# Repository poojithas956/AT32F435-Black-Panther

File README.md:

# AT32F435 - Black Panther

<h4>This is my most favorate Microcontroller, hence I wanted to design & build a compact, cute, powerful packed Dev Board. 

It features crucial sensors like ICM-42688-P for 6 axis Gyroscope, BMP581 for Barometric Pressure.

Can be used in wide variety of projects, powerful enough.
From being a custom microcontroller turned into a Flight controller, Can be used for Telemetry, IoT devices, Automation, etc...</h4>

## Layout

6 Layer PCB 4 mil / 4mil 

Stack:
Signal
Ground
Power
Ground
Signal

Consists 79 nets with 263 Pads, 142 Vias, 544 Track Segments

## Gallery

## Bill of Materials

| # | Item / MPN | Type | Vendor | Package | Qty | Unit Price | Line Total | Funding |
|---:|---|---|---|---|---:|---:|---:|---|
| 1 | [FRC0603F3571TS](https://www.lcsc.com/product-detail/C2933206.html) — 3.57kΩ ±1% 100mW 0603 Thick Film Resistor | Part | FOJAN | 0603 | 100 | $0.0012 | $0.12 | Grant |
| 2 | [X32258MOB4SI](https://www.lcsc.com/product-detail/C2682775.html) — Crystal 8MHz ±10ppm 12pF 150Ω SMD3225-4P | Part | YXC Crystal Oscillators | SMD3225-4P | 5 | $0.1993 | $1.00 | Grant |
| 3 | [AT32F435RGT7](https://www.lcsc.com/product-detail/C3029577.html) — ARM Cortex-M4 32 Bit 288MHz LQFP-64(10x10) Microcontrollers | Part | ARTERY | LQFP-64(10x10) | 1 | $4.3654 | $4.37 | Already own |
| 4 | [BQ24072RGTR](https://www.lcsc.com/product-detail/C140288.html) — 4.35V~6.6V Lithium Battery 1 1.5A QFN-16-EP(3x3) Battery Chargers RoHS | Part | TI | QFN-16-EP(3x3) | 1 | $1.0593 | $1.06 | Grant |
| 5 | [DFE252012P-1R0M=P2](https://www.lcsc.com/product-detail/C882955.html) — 4.3A 1uH ±20% 42mΩ 4.3A 1008 Fixed Inductors RoHS | Part | muRata | 1008 | 5 | $0.1244 | $0.62 | Grant |
| 6 | [TPS631000DRLR](https://www.lcsc.com/product-detail/C5219190.html) — Buck-Boost Switching Regulator IC Adjustable 1.2V~5.3V 2A SOT-583 | Part | TI | SOT-583 | 1 | $0.4560 | $0.46 | Grant |
| 7 | [TPD2EUSB30DRTR](https://www.lcsc.com/product-detail/C5182099.html) — 18VC Clamp TVS DIODE SOT(9x3) | Part | TECH PUBLIC | SOT(9x3) | 5 | $0.1979 | $0.99 | Grant |
| 8 | [BMP581](https://www.lcsc.com/product-detail/C5362283.html) — 30Kpa~1.25bar LGA-10(2x2) Pressure Sensors, Transducers RoHS | Part | Bosch | LGA-10(2x2) | 1 | $2.3423 | $2.34 | Grant |
| 9 | [ICM-42688-P](https://www.lcsc.com/product-detail/C1850418.html) — LGA-14(2.5x3) IMUs (Inertial Measurement Units) RoHS | Part | TDK InvenSense | LGA-14(2.5x3) | 1 | $25.8192 | $25.82 | Grant |
| 10 | [HX 3x4x2-2P-1.6N-04](https://www.lcsc.com/product-detail/C55073343.html) — 4mm 1.6N 12V 3mm Round Button SPST 50mA SMD Tactile Switch | Part | hanxia | SMD,4x3mm | 20 | $0.0274 | $0.55 | Grant |
| 11 | [CR16330J](https://www.lcsc.com/product-detail/C5602400.html) — 33Ω 100mW Thick Film Resistor ±100ppm/℃ ±5% 0603 Chip Resistor | Part | Meritek | 0603 | 1 | $0.0036 | $0.01 | Grant |
| 12 | [FRC0603F9102TS](https://www.lcsc.com/product-detail/C2907077.html) — 91kΩ ±1% 100mW 0603 Thick Film Resistor | Part | FOJAN | 0603 | 100 | $0.0016 | $0.16 | Grant |
| 13 | [RT0603BRD07511KL](https://www.lcsc.com/product-detail/C861454.html) — 511kΩ 100mW 75V Thin Film Resistor ±25ppm/℃ ±0.1% 0603 Chip Resistor | Part | YAGEO | 0603 | 20 | $0.0396 | $0.79 | Grant |
| 14 | [RC0603FR-074K7L](https://www.lcsc.com/product-detail/C99782.html) — 100mW 4.7kΩ 75V Thick Film Resistor ±100ppm/℃ ±1% 0603 Chip Resistor | Part | YAGEO | 0603 | 100 | $0.0032 | $0.32 | Grant |
| 15 | [RC0603FR-07100KL](https://www.lcsc.com/product-detail/C14675.html) — 100mW 100kΩ 75V Thick Film Resistor ±100ppm/℃ ±1% 0603 Chip Resistor | Part | YAGEO | 0603 | 100 | $0.0021 | $0.21 | Grant |
| 16 | [RC0603FR-071KL](https://www.lcsc.com/product-detail/C22548.html) — 100mW 1kΩ 75V Thick Film Resistor ±100ppm/℃ ±1% 0603 Chip Resistor | Part | YAGEO | 0603 | 100 | $0.0036 | $0.36 | Grant |
| 17 | [CL10A475KP8NNNC](https://www.lcsc.com/product-detail/C1705.html) — 4.7uF ±10% 10V Ceramic Capacitor X5R 0603 | Part | Samsung Electro-Mechanics | 0603 | 50 | $0.0128 | $0.64 | Grant |
| 18 | [RC0603FR-072K2L](https://www.lcsc.com/product-detail/C114662.html) — 100mW 2.2kΩ 75V Thick Film Resistor ±100ppm/℃ ±1% 0603 Chip Resistor | Part | YAGEO | 0603 | 100 | $0.0019 | $0.19 | Grant |
| 19 | [RC0603FR-0710KL](https://www.lcsc.com/product-detail/C98220.html) — 100mW 10kΩ 75V Thick Film Resistor ±100ppm/℃ ±1% 0603 Chip Resistor | Part | YAGEO | 0603 | 100 | $0.0023 | $0.23 | Grant |
| 20 | [FRC0603F5602TS](https://www.lcsc.com/product-detail/C2907053.html) — 56kΩ ±1% 100mW 0603 Thick Film Resistor | Part | FOJAN | 0603 | 100 | $0.0018 | $0.18 | Grant |
| 21 | [XL-1005UBC](https://www.lcsc.com/product-detail/C22355736.html) — Blue 465nm LED Indication - Discrete 3.3V 0402 | Part | XINGLIGHT | 0402 | 50 | $0.0081 | $0.41 | Grant |
| 22 | [XL-1005UGC](https://www.lcsc.com/product-detail/C965793.html) — Emerald Green 531nm LED Indication - Discrete 3V 0402 | Part | XINGLIGHT | 0402 | 50 | $0.0090 | $0.45 | Grant |
| 23 | [SZYY0603Y](https://www.lcsc.com/product-detail/C434424.html) — Yellow 596nm LED Indication - Discrete 2.4V 0603 | Part | Yongyu Photoelectric | 0603 | 50 | $0.0150 | $0.75 | Grant |
| 24 | [BLM18PG121SN1D](https://www.lcsc.com/product-detail/C14709.html) — 120Ω@100MHz 1 Line Ferrite Bead 0603 2A 50mΩ | Part | muRata | 0603 | 50 | $0.0142 | $0.71 | Grant |
| 25 | [PZ254V-11-04P](https://www.lcsc.com/product-detail/C2691448.html) — Pin Header 4 Position 2.54mm Pitch Single Row Through Hole -40℃~+105℃ | Part | XFCN | Through Hole,P=2.54mm | 20 | $0.0263 | $0.53 | Grant |
| 26 | [PZ254V-11-08P](https://www.lcsc.com/product-detail/C492407.html) — Pin Header 8 Position 2.54mm Pitch Single Row Through Hole -40℃~+105℃ | Part | XFCN | Through Hole,P=2.54mm | 10 | $0.0491 | $0.49 | Grant |
| 27 | [PH2.54-1X20P-H25](https://www.lcsc.com/product-detail/C42431804.html) — Pin Header 20 Position 2.54mm Pitch Single Row Through Hole -40℃~+105℃ | Part | JXTCONN | Through Hole,P=2.54mm | 5 | $0.0856 | $0.43 | Grant |
| 28 | [CL10A225KO8NNNC](https://www.lcsc.com/product-detail/C23630.html) — 2.2uF ±10% 16V Ceramic Capacitor X5R 0603 | Part | Samsung Electro-Mechanics | 0603 | 50 | $0.0101 | $0.51 | Grant |
| 29 | [CL10C150JB8NNNC](https://www.lcsc.com/product-detail/C1644.html) — 15pF ±5% 50V Ceramic Capacitor C0G 0603 | Part | Samsung Electro-Mechanics | 0603 | 50 | $0.0112 | $0.56 | Grant |
| 30 | [CL10B105KB8NQNC](https://www.lcsc.com/product-detail/C5199872.html) — 1uF ±10% 50V Ceramic Capacitor X7R 0603 | Part | Samsung Electro-Mechanics | 0603 | 20 | $0.0189 | $0.38 | Grant |
| 31 | [CL21A476MQYNNNE](https://www.lcsc.com/product-detail/C16780.html) — 47uF ±20% 6.3V Ceramic Capacitor X5R 0805 | Part | Samsung Electro-Mechanics | 0805 | 10 | $0.0750 | $0.75 | Grant |
| 32 | [CL21A226MAYNNNE](https://www.lcsc.com/product-detail/C602037.html) — 22uF ±20% 25V Ceramic Capacitor X5R 0805 | Part | Samsung Electro-Mechanics | 0805 | 10 | $0.1077 | $1.08 | Grant |
| 33 | [PCB](https://jlcpcb.com) | PCB | JLCPCB | — | 1 | $32.10 | $32.10 | Grant |
| 34 | [Stencil](https://jlcpcb.com) | PCB | JLCPCB | — | 1 | $7.22 | $7.22 | Grant |
| 35 | [Hot Plate](https://www.amazon.in/gp/product/B0C7W3W8C4/ref=ox_sc_act_title_1?smid=A2ON2B5XK3AL27&psc=1) | Part | Amazon | — | 1 | $33.18 | $33.18 | Grant |
| 36 | Shipping | Shipping | — | — | 1 | $8.99 | $8.99 | Grant |

**Overall total: $128.96**

**Grant total: $124.59**

## Notes
- Production / Fabrication files are inside `/production/`
- PCB files under `/PCB/`
- Datasheets under `/docs/`
- Bill of Material under `/BOM.csv`

## License
[MIT](/LICENSE)

Happy [Fabricating](https://fabricate.hackclub.com) ;D

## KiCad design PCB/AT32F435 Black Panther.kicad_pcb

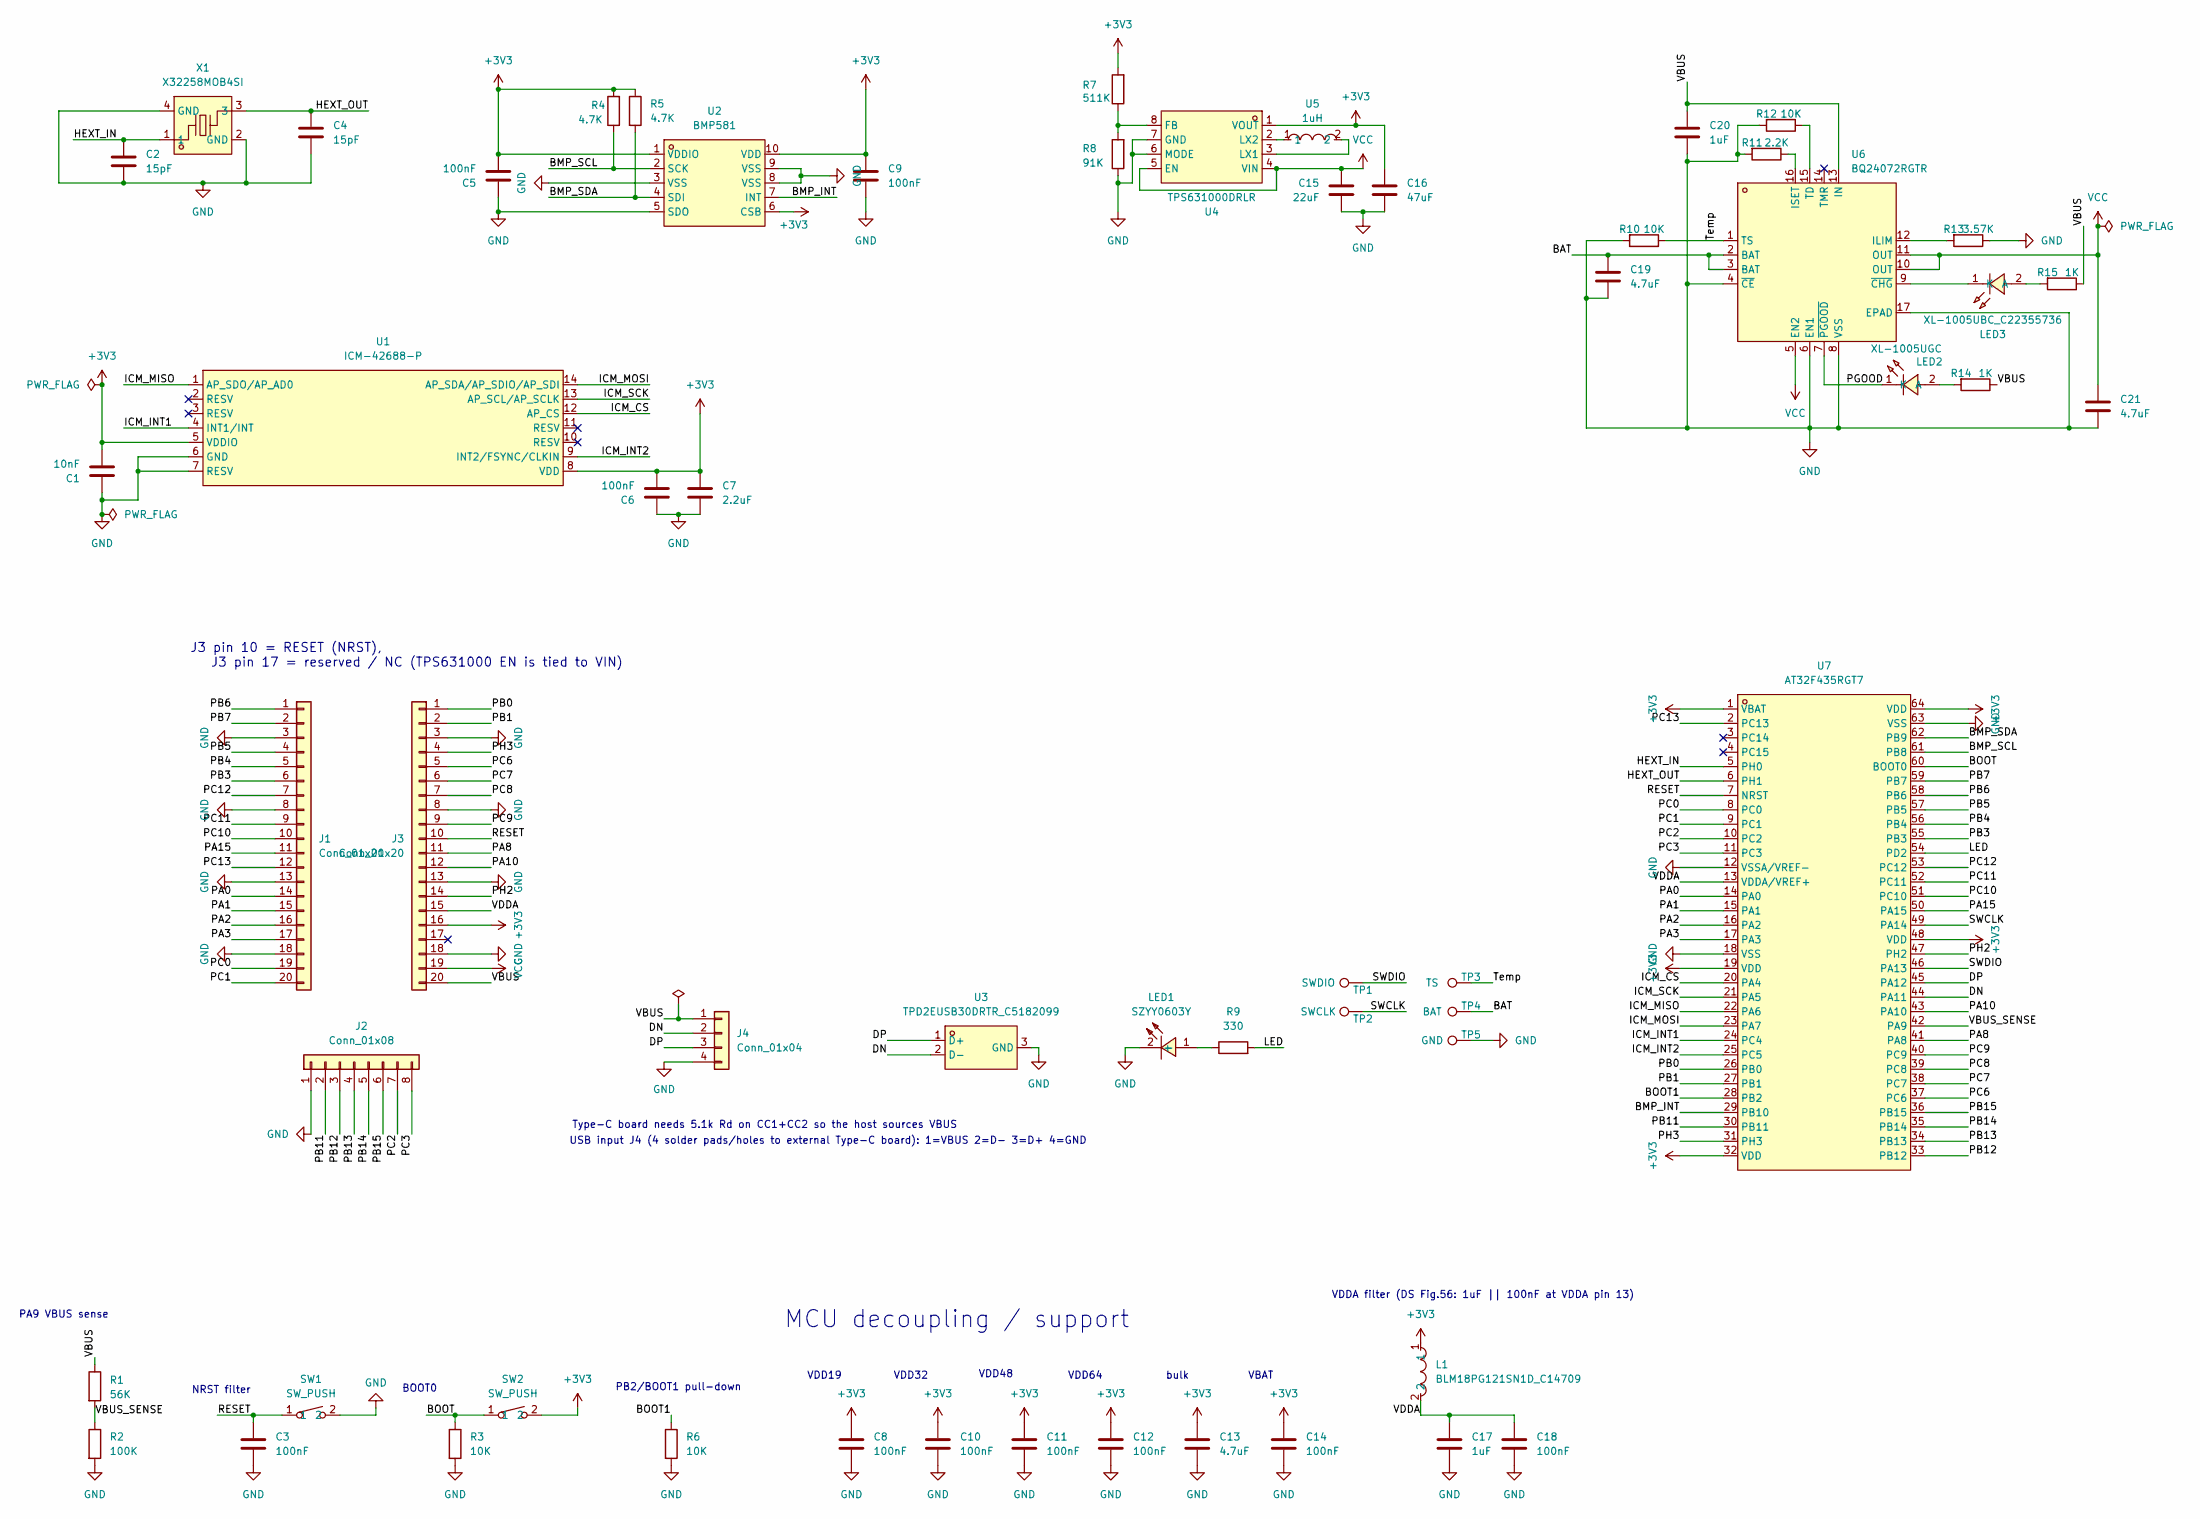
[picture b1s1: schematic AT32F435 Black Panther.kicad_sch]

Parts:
C1: 10nF; C_0603_1608Metric_Pad1.08x0.95mm_HandSolder
C2, C4: 15pF; C_0603_1608Metric_Pad1.08x0.95mm_HandSolder
C3, C5, C6, C8, C9, C10, C11, C12, C14, C18: 100nF; C_0603_1608Metric_Pad1.08x0.95mm_HandSolder
C7: 2.2uF; C_0603_1608Metric_Pad1.08x0.95mm_HandSolder
C13, C19, C21: 4.7uF; C_0603_1608Metric_Pad1.08x0.95mm_HandSolder
C15: 22uF; R_0805_2012Metric_Pad1.20x1.40mm_HandSolder
C16: 47uF; R_0805_2012Metric_Pad1.20x1.40mm_HandSolder
C17, C20: 1uF; C_0603_1608Metric_Pad1.08x0.95mm_HandSolder
J1, J3: Conn_01x20; PinHeader_1x20_P2.54mm_Vertical
J2: Conn_01x08; PinHeader_1x08_P2.54mm_Vertical
J4: Conn_01x04; PinHeader_1x04_P1.27mm_Vertical
L1: BLM18PG121SN1D_C14709; L0603; MPN BLM18PG121SN1D; LCSC Part C14709
LED1: SZYY0603Y; LED0603-R-RD_YELLOW; MPN SZYY0603Y; LCSC Part C434424
LED2: XL-1005UGC; LED0402-RD_GREEN; MPN XL-1005UGC; LCSC Part C965793
LED3: XL-1005UBC_C22355736; LED0402-RD; MPN XL-1005UBC; LCSC Part C22355736
R1: 56K; R_0603_1608Metric_Pad0.98x0.95mm_HandSolder
R2: 100K; R_0603_1608Metric_Pad0.98x0.95mm_HandSolder
R3, R6, R10, R12: 10K; R_0603_1608Metric_Pad0.98x0.95mm_HandSolder
R4, R5: 4.7K; R_0603_1608Metric_Pad0.98x0.95mm_HandSolder
R7: 511K; R_0603_1608Metric_Pad0.98x0.95mm_HandSolder
R8: 91K; R_0603_1608Metric_Pad0.98x0.95mm_HandSolder
R9: 330; R_0603_1608Metric_Pad0.98x0.95mm_HandSolder
R11: 2.2K; R_0603_1608Metric_Pad0.98x0.95mm_HandSolder
R13: 3.57K; R_0603_1608Metric_Pad0.98x0.95mm_HandSolder
R14, R15: 1K; R_0603_1608Metric_Pad0.98x0.95mm_HandSolder
SW1, SW2: SW_PUSH; SW-SMD_L4.0-W3.0-LS5.0; MPN HX 3x4x2-2P-1.6N-04; LCSC Part C55073343
TP1: SWDIO; TestPoint_Pad_D1.5mm
TP2: SWCLK; TestPoint_Pad_D1.5mm
TP3: TS; TestPoint_Pad_D1.0mm
TP4: BAT; TestPoint_Pad_D2.5mm
TP5: GND; TestPoint_Pad_D2.5mm
U1: ICM-42688-P; LGA-14_L3.0-W2.5-P0.50-TL; MPN ICM-42688-P; LCSC Part C1850418
U2: BMP581; LGA-10_L2.0-W2.0-P0.50-TL_BMP581; MPN BMP581; LCSC Part C5362283
U3: TPD2EUSB30DRTR_C5182099; SOT-723_L1.2-W0.8-P0.80-LS1.2-BR; MPN TPD2EUSB30DRTR; LCSC Part C5182099
U4: TPS631000DRLR; SOT-583-8_L2.1-W1.2-P0.50-LS1.6-BL; MPN TPS631000DRLR; LCSC Part C5219190
U5: 1uH; L1008; MPN DFE252012P-1R0M=P2; LCSC Part C882955
U6: BQ24072RGTR; QFN-16_L3.0-W3.0-P0.50-TL-EP; MPN BQ24072RGTR; LCSC Part C140288
U7: AT32F435RGT7; LQFP-64_L10.0-W10.0-P0.50-LS12.0-BL; MPN AT32F435RGT7; LCSC Part C3029577
X1: X32258MOB4SI; CRYSTAL-SMD_4P-L3.2-W2.5-BL; MPN X32258MOB4SI; LCSC Part C2682775

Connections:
+3V3: C1.2, C5.2, C6.2, C7.1, C8.1, C9.1, C10.1, C11.1, C12.1, C13.1, C14.1, C16.1, J3.16, L1.1, R4.2, R5.1, R7.2, SW2.2, U1.5 (VDDIO), U1.8 (VDD), U2.1 (VDDIO), U2.6 (CSB), U2.10 (VDD), U4.1 (VOUT), U7.1 (VBAT), U7.19 (VDD), U7.32 (VDD), U7.48 (VDD), U7.64 (VDD)
/BAT: C19.1, TP4.1 (1_1), U6.2 (BAT), U6.3 (BAT)
/BMP_INT: U2.7 (INT), U7.29 (PB10)
/BMP_SCL: R4.1, U2.2 (SCK), U7.61 (PB8)
/BMP_SDA: R5.2, U2.4 (SDI), U7.62 (PB9)
/BOOT: R3.1, SW2.1, U7.60 (BOOT0)
/BOOT1: R6.1, U7.28 (PB2)
/DN: J4.2, U3.2 (D-), U7.44 (PA11)
/DP: J4.3, U3.1 (D+), U7.45 (PA12)
/HEXT_IN: C2.1, U7.5 (PH0), X1.1
/HEXT_OUT: C4.1, U7.6 (PH1), X1.3
/ICM_CS: U1.12 (AP_CS), U7.20 (PA4)
/ICM_INT1: U1.4 (INT1/INT), U7.24 (PC4)
/ICM_INT2: U1.9 (INT2/FSYNC/CLKIN), U7.25 (PC5)
/ICM_MISO: U1.1 (AP_SDO/AP_AD0), U7.22 (PA6)
/ICM_MOSI: U1.14 (AP_SDA/AP_SDIO/AP_SDI), U7.23 (PA7)
/ICM_SCK: U1.13 (AP_SCL/AP_SCLK), U7.21 (PA5)
/LED: R9.2, U7.54 (PD2)
/PA0: J1.14, U7.14 (PA0)
/PA1: J1.15, U7.15 (PA1)
/PA2: J1.16, U7.16 (PA2)
/PA3: J1.17, U7.17 (PA3)
/PA8: J3.11, U7.41 (PA8)
/PA10: J3.12, U7.43 (PA10)
/PA15: J1.11, U7.50 (PA15)
/PB0: J3.1, U7.26 (PB0)
/PB1: J3.2, U7.27 (PB1)
/PB3: J1.6, U7.55 (PB3)
/PB4: J1.5, U7.56 (PB4)
/PB5: J1.4, U7.57 (PB5)
/PB6: J1.1, U7.58 (PB6)
/PB7: J1.2, U7.59 (PB7)
/PB11: J2.2, U7.30 (PB11)
/PB12: J2.3, U7.33 (PB12)
/PB13: J2.4, U7.34 (PB13)
/PB14: J2.5, U7.35 (PB14)
/PB15: J2.6, U7.36 (PB15)
/PC0: J1.19, U7.8 (PC0)
/PC1: J1.20, U7.9 (PC1)
/PC2: J2.7, U7.10 (PC2)
/PC3: J2.8, U7.11 (PC3)
/PC6: J3.5, U7.37 (PC6)
/PC7: J3.6, U7.38 (PC7)
/PC8: J3.7, U7.39 (PC8)
/PC9: J3.9, U7.40 (PC9)
/PC10: J1.10, U7.51 (PC10)
/PC11: J1.9, U7.52 (PC11)
/PC12: J1.7, U7.53 (PC12)
/PC13: J1.12, U7.2 (PC13)
/PGOOD: LED2.1 (K), U6.7 (~PGOOD)
/PH2: J3.14, U7.47 (PH2)
/PH3: J3.4, U7.31 (PH3)
/RESET: C3.1, J3.10, SW1.1, U7.7 (NRST)
/SWCLK: TP2.1 (1_1), U7.49 (PA14)
/SWDIO: TP1.1 (1_1), U7.46 (PA13)
/Temp: R10.1, TP3.1 (1_1), U6.1 (TS)
/VBUS: C20.1, J3.20, J4.1, R1.1, R14.1, R15.1, U6.13 (IN)
/VBUS_SENSE: R1.2, R2.1, U7.42 (PA9)
/VDDA: C17.1, C18.1, J3.15, L1.2, U7.13 (VDDA/VREF+)
GND: C1.1, C2.2, C3.2, C4.2, C5.1, C6.1, C7.2, C8.2, C9.2, C10.2, C11.2, C12.2, C13.2, C14.2, C15.1, C16.2, C17.2, C18.2, C19.2, C20.2, C21.2, J1.3, J1.8, J1.13, J1.18, J2.1, J3.3, J3.8, J3.13, J3.18, J4.4, LED1.2 (-), R2.2, R3.2, R6.2, R8.1, R10.2, R11.2, R12.2, R13.1, SW1.2, TP5.1 (1_1), U1.6 (GND), U1.7 (RESV), U2.3 (VSS), U2.5 (SDO), U2.8 (VSS), U2.9 (VSS), U3.3 (GND), U4.6 (MODE), U4.7 (GND), U6.4 (~CE), U6.6 (EN1), U6.8 (VSS), U6.17 (EPAD), U7.12 (VSSA/VREF-), U7.18 (VSS), U7.63 (VSS), X1.2 (GND), X1.4 (GND)
unnamed: LED1.1 (+), R9.1
unnamed: LED2.2 (A), R14.2
unnamed: LED3.2 (A), R15.2
unnamed: LED3.1 (K), U6.9 (~CHG)
unnamed: R7.1, R8.2, U4.8 (FB)
unnamed: U4.3 (LX1), U5.2
unnamed: U4.2 (LX2), U5.1
unnamed: R13.2, U6.12 (ILIM)
unnamed: R11.1, U6.16 (ISET)
unnamed: R12.1, U6.15 (TD)
VCC: C15.2, C21.1, J3.19, U4.4 (VIN), U4.5 (EN), U6.5 (EN2), U6.10 (OUT), U6.11 (OUT)

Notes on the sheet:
USB input J4 (4 solder pads/holes to external Type-C board): 1=VBUS 2=D- 3=D+ 4=GND
BOOT0
VDD19
J3 pin 10 = RESET (NRST), J3 pin 17 = reserved / NC (TPS631000 EN is tied to VIN)
PB2/BOOT1 pull-down
VDDA filter (DS Fig.56: 1uF || 100nF at VDDA pin 13)
MCU decoupling / support
VBAT
VDD48
PA9 VBUS sense
VDD64
Type-C board needs 5.1k Rd on CC1+CC2 so the host sources VBUS
NRST filter
bulk
VDD32

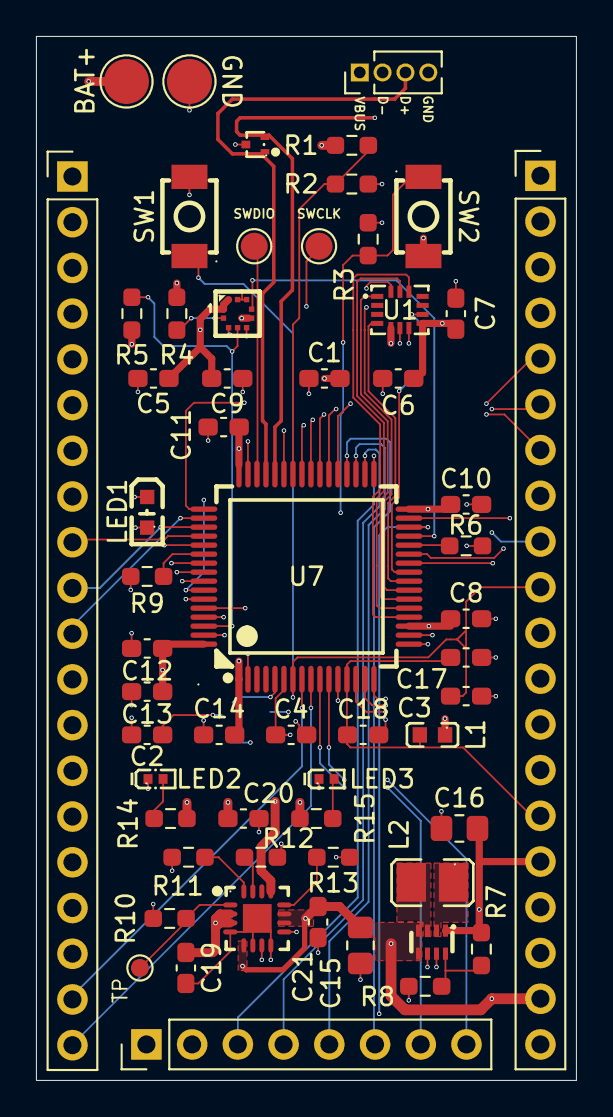
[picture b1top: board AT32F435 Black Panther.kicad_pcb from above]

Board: 6 copper layers, 30.0 x 58.0 mm, 59 parts (1 on the bottom side), 71 nets.

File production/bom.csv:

Designator,Footprint,Quantity,Value,LCSC Part #
C1,0603,1,10nF,
"C10, C11, C12, C14, C18, C3, C5, C6, C8, C9",0603,10,100nF,
"C13, C19, C21",0603,3,4.7uF,
C15,0805,1,22uF,
C16,0805,1,47uF,
"C17, C20",0603,2,1uF,
"C2, C4",0603,2,15pF,
C7,0603,1,2.2uF,
"J1, J3",PinHeader_1x20_P2.54mm_Vertical,2,Conn_01x20,
J2,PinHeader_1x08_P2.54mm_Vertical,1,Conn_01x08,
J4,PinHeader_1x04_P1.27mm_Vertical,1,Conn_01x04,
L1,L0603,1,BLM18PG121SN1D_C14709,C14709
LED1,LED0603-R-RD_YELLOW,1,SZYY0603Y,C434424
LED2,LED0402-RD_GREEN,1,XL-1005UGC,C965793
LED3,LED0402-RD,1,XL-1005UBC_C22355736,C22355736
R1,0603,1,56K,
"R10, R12, R3, R6",0603,4,10K,
R11,0603,1,2.2K,
R13,0603,1,3.57K,
"R14, R15",0603,2,1K,
R2,0603,1,100K,
"R4, R5",0603,2,4.7K,
R7,0603,1,511K,
R8,0603,1,91K,
R9,0603,1,330,
"SW1, SW2",SW-SMD_L4.0-W3.0-LS5.0,2,SW_PUSH,C55073343
TP1,TestPoint_Pad_D1.5mm,1,SWDIO,
TP2,TestPoint_Pad_D1.5mm,1,SWCLK,
TP3,TestPoint_Pad_D1.0mm,1,TS,
TP4,TestPoint_Pad_D2.5mm,1,BAT,
TP5,TestPoint_Pad_D2.5mm,1,GND,
U1,LGA-14_L3.0-W2.5-P0.50-TL,1,ICM-42688-P,C1850418
U2,LGA-10_L2.0-W2.0-P0.50-TL_BMP581,1,BMP581,C5362283
U3,SOT-723_L1.2-W0.8-P0.80-LS1.2-BR,1,TPD2EUSB30DRTR_C5182099,C5182099
U4,SOT-583-8_L2.1-W1.2-P0.50-LS1.6-BL,1,TPS631000DRLR,C5219190
U5,L1008,1,1uH,C882955
U6,QFN-16_L3.0-W3.0-P0.50-TL-EP,1,BQ24072RGTR,C140288
U7,LQFP-64_L10.0-W10.0-P0.50-LS12.0-BL,1,AT32F435RGT7,C3029577
X1,CRYSTAL-SMD_4P-L3.2-W2.5-BL,1,X32258MOB4SI,C2682775
